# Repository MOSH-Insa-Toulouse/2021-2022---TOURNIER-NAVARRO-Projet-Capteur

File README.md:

# 2021-2022---TOURNIER-NAVARRO-Projet-Capteur
Ce projet s'inclut au sein de l'UF "Du capteur au banc de test en open source hardware" dont le but est de travailler sur l'ensemble des étapes de réalisation d'un capteur à technologie low-tech. 

Notre projet se base sur des travaux de recherches d'un capteur de déformation type jauge de contrainte réalisé à partir de graphite. Il est déposé à l'aide d'un crayon B12 sur une feuille de papier. L'objectif est de pouvoir mesurer la résistance de ce capteur et son évolution au cours du temps en fonction de sa déformation. 

Pour cela, nous avons réalisé un PCB Shield grace au logiciel Kicad. Il regroupe un circuit analogique de type amplificateur transimpédance, un écran OLED, un encodeur rotatoire et un module Bluetooth. Ce PCB sera pluggé sur un microcontroleur Arduino UNO dans le but d'afficher la valeur de résistance sur l'écran et son évolution dans le temps sur une application smartphone.

Ce dispositif pourra nous permettre par la suite de réaliser une datasheet et un banc de test associé au capteur afin d'en faire une analyse critique.

## Sommaire

* [1. Introduction](#1-introduction)
* [2. Circuit électronique](#2-circuit-électronique)
  * [2.1. Schéma du circuit](#21-schéma-du-circuit)
  * [2.2. Réponse transitoire et fréquentielle](#22-réponse-transitoire-et-fréquentielle)
  * [2.3. Filtres](#23-filtres)
  * [2.4. Modélisation du capteur](#24-modélisation-du-capteur)
* [3. KiCad](#3-kicad)
  * [3.1. Schématique](#31-schématique)
  * [3.2. Edition du PCB](#32-edition-du-pcb)
  * [3.3. Visualisation 3D](#33-visualisation-3d)
* [4. Arduino](#4-arduino)
  * [4.1. Environnement utilisé](#41-environnement-utilisé)
  * [4.2. Librairies utilisées](#42-librairies-utilisées)
  * [4.3. Code Arduino](#43-code-arduino)
* [5. Application Bluetooth](#5-application-bluetooth)
* [6. Banc de test](#6-banc-de-test)
  * [6.1. Pièce 3D](#61-pièce-3d) 
  * [6.2. Ballons de sport](#62-ballons-de-sport)
* [7. Datasheet](#7-datasheet)

## 1. Introduction

Le capteur de déformation que nous avons crée ne représente qu'un outil permettant de récolter des données. Il est indispensable d'y ajouter une électronique et une programmation afin de pouvoir les traiter et en tirer une conclusion. Ce projet se divise donc en plusieurs étapes afin de pouvoir récupérer et analyser au mieux ces valeurs de résistances délivrées.

- [Circuit électronique](https://github.com/MOSH-Insa-Toulouse/2021-2022---TOURNIER-NAVARRO-Projet-Capteur/tree/main/LTspice) : Le signal délivré par le capteur est un courant très faible. Nous avons dimensionner un circuit à l'aide du logiciel LTspice qui permet d'amplifier et de lisser le signal à partir d'amplificateur et de filtre. En sortie, nous obtenons un signal compris entre 0 et 5V.

- [PCB SHIELD](https://github.com/MOSH-Insa-Toulouse/2021-2022---TOURNIER-NAVARRO-Projet-Capteur/tree/main/KiCad) : Nous avons fabriqué une carte électronique afin de pouvoir y regrouper tous les composants permettant de traiter les données du capteur.

- [Code Arduino](https://github.com/MOSH-Insa-Toulouse/2021-2022---TOURNIER-NAVARRO-Projet-Capteur/tree/main/Arduino) : Ce programme nous permet de controler les différents composants présents sur notre SHIELD et de transformer notre valeur de tension en une valeur de résistance. Cette valeur sera affichée sur un écran OLED dont ces menus seront controlées par un encodeur rotatoire. A partir d'un module Bluetooth, nous pourrons ensuite envoyer cette donnée sur une application.

- [Application](https://github.com/MOSH-Insa-Toulouse/2021-2022---TOURNIER-NAVARRO-Projet-Capteur/tree/main/Application) : A partir du site MIT, nous avons codé une application Android qui affiche un graphique de l'évolution de la résistance du capteur en fonction du temps.

- [Banc de test](https://github.com/MOSH-Insa-Toulouse/2021-2022---TOURNIER-NAVARRO-Projet-Capteur/blob/main/README.md#6-banc-de-test) : Dans le but de caractériser notre capter, notre banc de test se compose d'une pièces 3D et de ballons de sport avec des rayons de courbure différents.

- [Datasheet](https://github.com/MOSH-Insa-Toulouse/2021-2022---TOURNIER-NAVARRO-Projet-Capteur/blob/main/Datasheet%20capteur%20graphite.docx) : Document reprenant l'ensemble des caractéristiques de notre capteur de déformation. 

## 2. Circuit électronique

### 2.1 Schéma du circuit

Dans le cas du capteur de déformation que nous voulons créer, le signal délivré est de courant très faible : de l'ordre de 100 nA. Cela pose un problème car le microcontroleur ne peut pas mesurer directement ce courant à cause d'une impédance d'entrée trop élevée.

La solution mise en place afin de palier ce problème est d'utiliser un amplificateur transimpédance suivi d'un étage amplificateur inverseur. 

Plusieurs filtres sont aussi indispensables afin de pouvoir extraire l'information utile du capteur : Un filtre capteur afin de limiter les bruits en courant (f1=10Hz) , un filtre passe bas pour les bruits du secteur à 50Hz (f2 = quelques Hz) et un filtre en sortie pour l'échantillonage. Notre Arduino possède une fréquence d'échantillonage de 10kHz environ donc notre signal sera filtré au maximum à 5kHz pour respecter le critère de Shannon.

Schéma suggéré 

Le générateur de tension envoyant un signal sinusoidal et associé à la capacité parasité C5 vient simuler le bruit du secteur.

### 2.2 Réponse transitoire et fréquentielle

En appliquant un PULSE en régime transitoire, on peut bien observer l'action de l'amplificateur transimpédance puis celui de l'étage inverseur :

Notre but est de vérifier si le gain du montage est cohérent avec ce que l'on souhaite obtenir en sortie. Nous allons donc effectuer une simulation fréquentielle en imposant un signal AC :

On observe un gain à basse fréquence de +140 dB ce qui nous ramène à un gain G=VAOC/Isens = 10^7 ce qui est bien cohérent avec le passage de 100nA à 1V.

### 2.3 Filtres 

Nous avons ensuite étudier les fréquences de coupure de chaque filtre pour voir s'ils jouaient bien leur rôle. Pour cela, on fait des simulations fréquentielles tout en ne laissant qu'une capacité active.

- Filtre d'entrée (R5 associée à C1) 

On obtient à -3dB, une fréquence de coupure de 16Hz ce qui fonctionne plutot bien pour l'entrée du capteur. Cepdendant, notre fc est perturbée par la présence de R1 derrière.

- Filtre pour le secteur (R3 associée à C4)

On obtient à -3dB, une fréquence de coupure compriise entre 1 et 2Hz ce qui permet de couper le bruit induit par le secteur 50Hz.

- Filtre de sortie (R6 associée à C2)

On obtient à -3dB, une fréquence de coupure de 1,6kHz ce qui fonctionne bien pour l'échantillonage de l'ARDUINO.

### 2.4 Modélisation du capteur

Pour modéliser notre capteur, nous avons créé un nouveau composant qui est un générateur arbitraire avec une expression du courant : 

Ce modèle permet d'appliquer un signal qui varie comme le capteur.

## 3. Kicad

Nous avons utilisé le logiciel KiCad qui permet de réaliser des schémas électroniques et des circuits imprimés. Nous avons réalisé un SHIELD où l'ensemble des composants sera déposé dessus. Il sera ensuite pluggé directement sur l'arduino. 
La réalisation d'un PCB se divise en 3 étapes : Le schématique, l'édition du PCB et sa visualisation 3D

### 3.1. Schématique

La base du circuit électronique repose sur la création du schématique. Les symboles et empreintes du module arduino UNO, des résistances et des capacités sont disponibles dans les librairies installées sur KiCad. Cependant, il nous a fallu créer une librairie d'empreinte pour l'ensemble des autres composants. Les empreintes devaient respecter les pins physiques pour que le routage se passe correctement par la suite.

- Ecran OLED

- Amplificateur LTC

- Module Bluetooth

- Encodeur rotatoire

- Schématique entière

### 3.2. Edition du PCB

Après avoir associé chaque empreinte à son symbole pour tous les composants, nous avons édité le circuit imprimé. La partie la plus complexe consiste à répartir les composants sur le PCB et router correctement les connexions entre chaque pin.

### 3.3. Visualisation 3D

Afin de vérifier si nos composants peuvent bien s'implémenter sur le SHIELD, nous pouvons utiliser la visualisation 3D pour voir s'ils ne se genent pas entre eux ou s'il n'empietent pas sur les pins arduino.
Les empreintes 3D pour les résistances et capacité sont disponible sur KiCaD. Il faut aller chercher en ligne les empreintes 3D pour le module blutetooth, l'encodeur et l'écran OLED.

## 4. Arduino

### 4.1 Environnement utilisé
Notre projet capteur s'est construit sur la base d'une plateforme Arduino UNO (voir image ci dessous).

Notre code a été écris sous la version Arduino IDE 1.8.19. 

### 4.2 Librairies utilisées
Nous avons utilisé la librairie "SoftwareSerial.h" pour le module bluetooth ainsi que la librairie "Adafruit_SSD1306.h" pour le module OLED.

### 4.3 Code Arduino
Notre programme arduino nous permet de récupérer la valeur de la tension de notre capteur, calculer la résistance qui en résulte, l'afficher sur l'écran OLED et envoyer ces données via bluetooth sur notre application Android. Nous avons également ajouté un encodeur rotatoire qui nous permet de nous balade sur un menu affiché à l'écran OLED (3 options possibles: la valeur de la tension, la valeur de la résistance et un message surprise). 

- Nous définissons tout d'abord des variables qui nous serviront à initialiser les paramètres du bluetooth, de l'encodeur rotatoire (et bouton poussoir) et de l'écran OLED (appel des librairies, définitions des pins arduinos utilisés pour les différents modules etc...) ainsi que des variables qui nous serviront à calculer la résistance de notre capteur. 

- Ensuite nous avons créer une fonction setup qui initialise les paramètres des différents modules.

- Nous avons également créer une fonction pour récupérer la valeur de la tension du capteur, une fonction pour calculer la valeur de la résistance, une fonction debouncing de l'encodeur rotatoire pour pouvoir se balader de manière régulière sur le menu, une fonction qui permet de sélectionner un menu en fonction de la position du curseur, des fonctions affichant le menu principal et déroulant (on surligne la ligne sur laquelle se trouve le curseur), et enfin une fonction permettant d'afficher les sous-menus.

- Pour terminer nous avons créé une boucle "loop" qui affiche les différentes données en fonction de là où se trouve le curseur avec différents "if" grâce aux fonctions créées en amont. 

## 5. Application Bluetooth
L'application Android a été codé sur le site internet MIT App Inventor. Ce site internet permet de manière intuitive de créer des applications mobiles simples téléchargeables seulement via des téléphones Androids en scannant un QR code généré par le site. 
Cette application va nous permettre d'afficher sur un téléphone mobile les valeurs de la tension et de la résistance délivrées par le capteur graphène en temps réel, ainsi qu'afficher une courbe représentant l'évolution de la tension reçue en fonction de temps (en pliant plus ou moins le capteur nous pourrons observer en direct l'évolution de la tensions dans le temps).

Notre application est composée : 
- d'un bouton bluetooth permettant à l'utilisateur de se connecter au module blutooth de notre carte Arduino
- d'un canva qui permet d'afficher la courbe de la tension en fonction du temps 
- deux encadrés textes qui affichent respectivement la valeur de la tensions et de la résistance

Voilà un apperçu de la face avant de notre application : 

## 6. Banc de test

Le banc de test est la partie du projet qui permet de caractériser notre capteur. Le principe est de créer un protocole expérimental afin de tester la réponse du capteur en fonction des contraintes qu'on va lui appliquer.

Nous avons réalisé 2 bancs de test à partir d'une pièce 3D et de ballons de sport.

### 6.1. Pièce 3D

Ce banc de test se base sur une pièce 3D imprimée par les élèves des années antérieures. Elle est composée de plusieurs demi-cercles de rayons différents afin de tester le capteur en flexion et en compression.

Pour plus de détails sur le protocole et la manière de calculer la déformation induite par ce banc de test voir la datasheet ()

### 6.2. Ballons de sport

Dans le but de valider le modèle du capteur, nous avons relevés les valeurs de résistance du capteur sur des rayons de courbure connues. L'idée que nous avons eut est d'utiliser des balles de sport dont les dimensions sont conventionnées.

On fait ici une sorte de cheminement inverse en essayant de retrouver le rayon de courbure à partir de la valeur de la résistance et vérifier si notre capteur est bien fiable. Tout le protocole est disponible dans la datasheet du capteur : [Datasheet](https://github.com/MOSH-Insa-Toulouse/2021-2022---TOURNIER-NAVARRO-Projet-Capteur/blob/main/Datasheet%20capteur%20graphite.docx)

## 7. Datasheet

A l'aide des bancs de test réalisés, nous avons pu caractériser notre capteur en utilisant un crayon HB. Toutes les données sont à retrouver dans la [Datasheet](https://github.com/MOSH-Insa-Toulouse/2021-2022---TOURNIER-NAVARRO-Projet-Capteur/blob/main/Datasheet%20capteur%20graphite.docx)

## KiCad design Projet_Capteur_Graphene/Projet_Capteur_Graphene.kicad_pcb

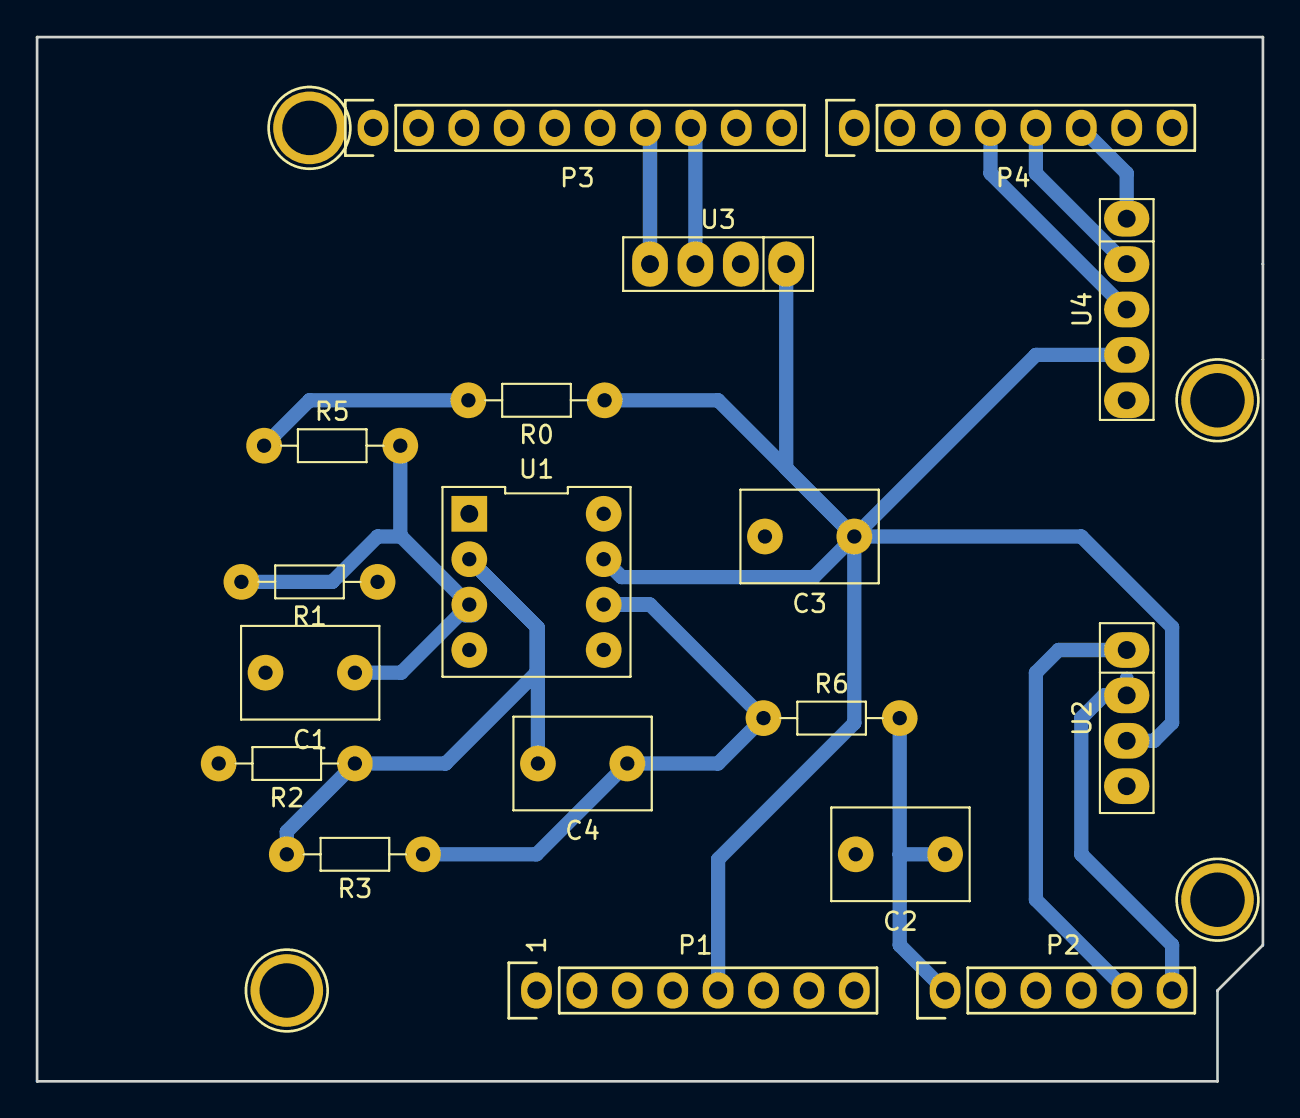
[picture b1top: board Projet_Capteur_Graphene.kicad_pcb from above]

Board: 2 copper layers, 68.6 x 58.4 mm, 22 parts (0 on the bottom side), 14 nets.

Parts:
C1, C2, C3: 100n; C_Disc_D7.5mm_W5.0mm_P5.00mm
C4: 1µ; C_Disc_D7.5mm_W5.0mm_P5.00mm
P1: Power; Socket_Strip_Arduino_1x08
P2: Analog; Socket_Strip_Arduino_1x06
P3: Digital; Socket_Strip_Arduino_1x10
P4: Digital; Socket_Strip_Arduino_1x08
P5, P6, P7, P8: CONN_01X01; Arduino_1pin
R0: Rsensor; R_Axial_DIN0204_L3.6mm_D1.6mm_P7.62mm_Horizontal
R1, R3: 100k; R_Axial_DIN0204_L3.6mm_D1.6mm_P7.62mm_Horizontal
R2, R6: 1k; R_Axial_DIN0204_L3.6mm_D1.6mm_P7.62mm_Horizontal
R5: 10k; R_Axial_DIN0204_L3.6mm_D1.6mm_P7.62mm_Horizontal
U1: LTC1050; DIP-8_296
U2: OLED_0.91; SIP-4
U3: Bluetooth-HC05; Bluetooth
U4: KY-040

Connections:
+5V: C3.1, P1.5, R0.1, U1.7 (V+), U2.2 (VCC), U3.1 (VCC), U4.4 (VCC)
ADC: C2.1, P2.1, R6.2
CLK: P4.6, U4.1 (CLK)
DATA: P4.5, U4.2 (DATA)
GND: C1.2, C2.2, C3.2, P1.6, P1.7, P3.4, R1.1, R2.2, U1.4 (V-), U2.1 (GND), U3.2 (GND), U4.5 (GND)
IN+: C1.1, R1.2, R5.2, U1.3 (+IN)
IN-: C4.2, R2.1, R3.2, U1.2 (-IN)
unnamed: C4.1, R3.1, R6.1, U1.6 (OUT)
unnamed: R0.2, R5.1
RX: P3.8, U3.3 (TX_to_RX_(arduino))
SCK: P2.6, P3.1, U2.3 (SCK)
SDA: P2.5, P3.2, U2.4 (SDA)
SWITCH: P4.4, U4.3 (SWITCH)
TX: P3.7, U3.4 (RX_to_TX_(arduino))

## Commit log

2022-04-18 Create KiCad
2022-04-18 Partie KiCad
2022-04-18 Code Arduino
2022-04-18 LTspice
2022-04-18 Application
2022-04-18 README
